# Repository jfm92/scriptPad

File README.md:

# scriptPad

The scriptPad project is a macroPad fully customizable with build in USB WebPage allowing to configure every aspect of the device without extra software or web page, everything you need in a single device.

## Work in progess

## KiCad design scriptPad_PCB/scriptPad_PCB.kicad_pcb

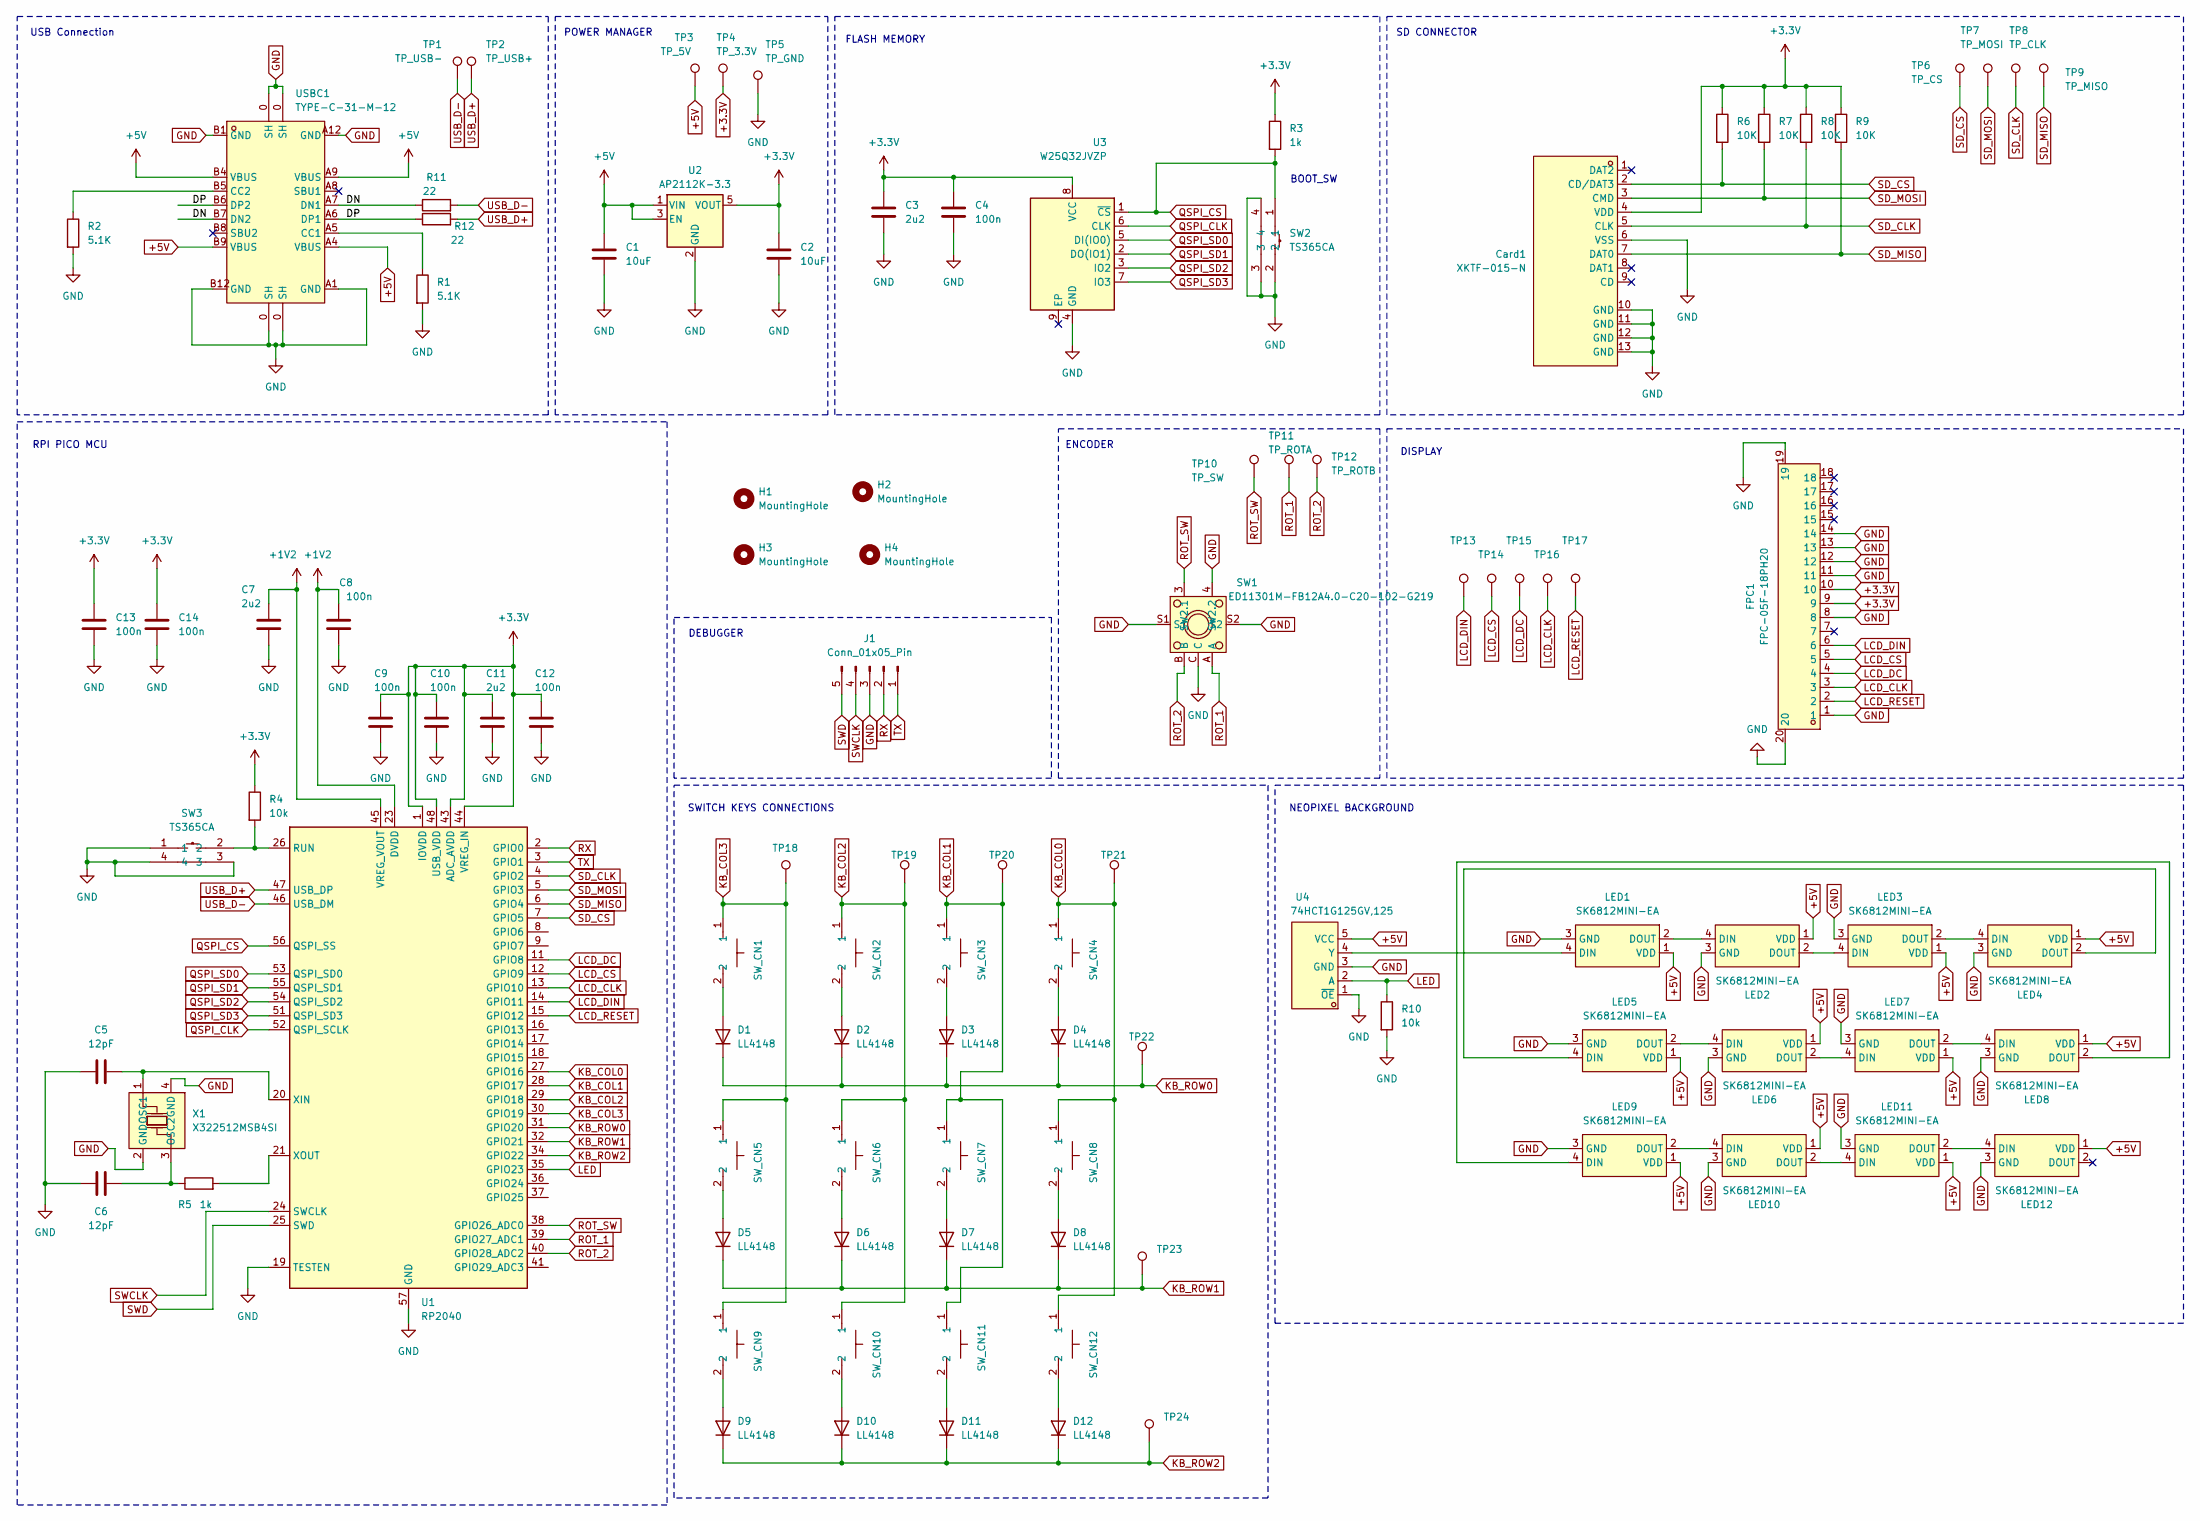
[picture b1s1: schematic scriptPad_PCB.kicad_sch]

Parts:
C1, C2: 10uF; C_0805_2012Metric; LCSC C17024
C3: 2u2; C_0805_2012Metric; LCSC C19110
C4: 100n; C_0603_1608Metric; LCSC C1591
C5, C6: 12pF; C_0603_1608Metric
C7, C11: 2u2; C_0805_2012Metric
C8, C9, C10, C12, C13, C14: 100n; C_0603_1608Metric
Card1: XKTF-015-N; TF-SMD_XKTF-015-N; LCSC Part C381082
D1: LL4148; D_MiniMELF; LCSC C2891733
D2, D3, D4, D5, D6, D7, D8, D9, D10, D11, D12: LL4148; D_MiniMELF
FPC1: FPC-05F-18PH20; FPC-SMD_18P-P0.50_FPC-05F-18PH20; LCSC Part C2856802
H1, H2, H3, H4: MountingHole; MountingHole_2.7mm_M2.5_Pad
J1: Conn_01x05_Pin; PinHeader_1x05_P1.27mm_Vertical
LED1, LED2, LED3, LED4, LED5, LED6, LED7, LED8, LED9, LED10, LED11, LED12: SK6812MINI-EA; LED-SMD_4P-L3.2-W2.8_SK6812MINI-EA; LCSC Part C5378731
R1, R2: 5.1K; R_0603_1608Metric; LCSC C156350
R3, R5: 1k; R_0805_2012Metric
R4, R10: 10k; R_0805_2012Metric
R6, R7, R8, R9: 10K; R_0805_2012Metric
R11, R12: 22; R_0603_1608Metric; LCSC C25295
SW1: ED11301M-FB12A4.0-C20-102-G219; SW-TH_CTR_ED11301M-FB12A4.0-C20-102-G219; LCSC Part C18213487
SW2, SW3: TS365CA; SW-SMD_TS365CA; LCSC Part C2681480
SW_CN1, SW_CN2, SW_CN3, SW_CN4, SW_CN5, SW_CN6, SW_CN7, SW_CN8, SW_CN9, SW_CN10, SW_CN11, SW_CN12: CPG151101S11-16; SMD_KEYBOARD-SW; LCSC Part C5156480
TP1: TP_USB-; TestPoint_Pad_D2.0mm
TP2: TP_USB+; TestPoint_Pad_D2.0mm
TP3: TP_5V; TestPoint_Pad_D2.0mm
TP4: TP_3.3V; TestPoint_Pad_D2.0mm
TP5: TP_GND; TestPoint_Pad_D2.0mm
TP6: TP_CS; TestPoint_Pad_D2.0mm
TP7: TP_MOSI; TestPoint_Pad_D2.0mm
TP8: TP_CLK; TestPoint_Pad_D2.0mm
TP9: TP_MISO; TestPoint_Pad_D2.0mm
TP10: TP_SW; TestPoint_Pad_D2.0mm
TP11: TP_ROTA; TestPoint_Pad_D2.0mm
TP12: TP_ROTB; TestPoint_Pad_D2.0mm
TP13, TP14, TP15, TP16, TP17, TP18, TP19, TP20, TP21, TP22, TP23, TP24: TestPoint; TestPoint_Pad_D2.0mm
U1: RP2040; QFN-56-1EP_7x7mm_P0.4mm_EP3.2x3.2mm
U2: AP2112K-3.3; SOT-23-5; LCSC C51118
U3: W25Q32JVZP; WSON-8-1EP_6x5mm_P1.27mm_EP3.4x4.3mm
U4: 74HCT1G125GV,125; SOT-753_L3.1-W1.7-P0.95-LS3.0-BL; LCSC Part C12502
USBC1: TYPE-C-31-M-12; USB-C_SMD-TYPE-C-31-M-12; LCSC Part C165948
X1: X322512MSB4SI; OSC-SMD_4P-L3.2-W2.5-BL; LCSC Part C9002

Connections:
+1V2: C7.1, C8.1, U1.23 (DVDD), U1.45 (VREG_VOUT), U1.50 (DVDD)
+3.3V: C2.1, C3.1, C4.1, C9.1, C10.1, C11.1, C12.1, C13.1, C14.1, Card1.4 (VDD), FPC1.9, FPC1.10, R3.1, R4.1, R6.1, R7.1, R8.1, R9.1, TP4.1, U1.1 (IOVDD), U1.10 (IOVDD), U1.22 (IOVDD), U1.33 (IOVDD), U1.42 (IOVDD), U1.43 (ADC_AVDD), U1.44 (VREG_IN), U1.48 (USB_VDD), U1.49 (IOVDD), U2.5 (VOUT), U3.8 (VCC)
+5V: C1.1, LED1.1 (VDD), LED2.1 (VDD), LED3.1 (VDD), LED4.1 (VDD), LED5.1 (VDD), LED6.1 (VDD), LED7.1 (VDD), LED8.1 (VDD), LED9.1 (VDD), LED10.1 (VDD), LED11.1 (VDD), LED12.1 (VDD), TP3.1, U2.1 (VIN), U2.3 (EN), U4.5 (VCC), USBC1.A4 (VBUS), USBC1.A9 (VBUS), USBC1.B4 (VBUS), USBC1.B9 (VBUS)
/DN: R11.1, USBC1.A7 (DN1), USBC1.B7 (DN2)
/DP: R12.1, USBC1.A6 (DP1), USBC1.B6 (DP2)
GND: C1.2, C2.2, C3.2, C4.2, C5.2, C6.2, C7.2, C8.2, C9.2, C10.2, C11.2, C12.2, C13.2, C14.2, Card1.6 (VSS), Card1.10 (GND), Card1.11 (GND), Card1.12 (GND), Card1.13 (GND), FPC1.1, FPC1.8, FPC1.11, FPC1.12, FPC1.13, FPC1.14, FPC1.19, FPC1.20, J1.3, LED1.3 (GND), LED2.3 (GND), LED3.3 (GND), LED4.3 (GND), LED5.3 (GND), LED6.3 (GND), LED7.3 (GND), LED8.3 (GND), LED9.3 (GND), LED10.3 (GND), LED11.3 (GND), LED12.3 (GND), R1.2, R2.2, R10.2, SW1.4 (SW2.2), SW1.C, SW1.S1, SW1.S2, SW2.2, SW2.3, SW2.4, SW3.1, SW3.3, SW3.4, TP5.1, U1.19 (TESTEN), U1.57 (GND), U2.2 (GND), U3.4 (GND), U4.1 (~OE), U4.3 (GND), USBC1.0 (SH), USBC1.A1 (GND), USBC1.A12 (GND), USBC1.B1 (GND), USBC1.B12 (GND), X1.2 (GND), X1.4 (GND)
KB_COL0: SW_CN4.1, SW_CN8.1, SW_CN12.1, TP21.1, U1.27 (GPIO16)
KB_COL1: SW_CN3.1, SW_CN7.1, SW_CN11.1, TP20.1, U1.28 (GPIO17)
KB_COL2: SW_CN2.1, SW_CN6.1, SW_CN10.1, TP19.1, U1.29 (GPIO18)
KB_COL3: SW_CN1.1, SW_CN5.1, SW_CN9.1, TP18.1, U1.30 (GPIO19)
KB_ROW0: D1.1 (K), D2.1 (K), D3.1 (K), D4.1 (K), TP22.1, U1.31 (GPIO20)
KB_ROW1: D5.1 (K), D6.1 (K), D7.1 (K), D8.1 (K), TP23.1, U1.32 (GPIO21)
KB_ROW2: D9.1 (K), D10.1 (K), D11.1 (K), D12.1 (K), TP24.1, U1.34 (GPIO22)
LCD_CLK: FPC1.3, TP16.1, U1.13 (GPIO10)
LCD_CS: FPC1.5, TP14.1, U1.12 (GPIO9)
LCD_DC: FPC1.4, TP15.1, U1.11 (GPIO8)
LCD_DIN: FPC1.6, TP13.1, U1.14 (GPIO11)
LCD_RESET: FPC1.2, TP17.1, U1.15 (GPIO12)
LED: R10.1, U1.35 (GPIO23), U4.2 (A)
unnamed: D1.2 (A), SW_CN1.2
unnamed: D2.2 (A), SW_CN2.2
unnamed: D3.2 (A), SW_CN3.2
unnamed: D4.2 (A), SW_CN4.2
unnamed: D5.2 (A), SW_CN5.2
unnamed: D6.2 (A), SW_CN6.2
unnamed: D7.2 (A), SW_CN7.2
unnamed: D8.2 (A), SW_CN8.2
unnamed: D9.2 (A), SW_CN9.2
unnamed: D10.2 (A), SW_CN10.2
unnamed: D11.2 (A), SW_CN11.2
unnamed: D12.2 (A), SW_CN12.2
unnamed: LED1.4 (DIN), U4.4 (Y)
unnamed: LED1.2 (DOUT), LED2.4 (DIN)
unnamed: LED2.2 (DOUT), LED3.4 (DIN)
unnamed: LED3.2 (DOUT), LED4.4 (DIN)
unnamed: LED4.2 (DOUT), LED5.4 (DIN)
unnamed: LED5.2 (DOUT), LED6.4 (DIN)
unnamed: LED6.2 (DOUT), LED7.4 (DIN)
unnamed: LED7.2 (DOUT), LED8.4 (DIN)
unnamed: LED8.2 (DOUT), LED9.4 (DIN)
unnamed: LED9.2 (DOUT), LED10.4 (DIN)
unnamed: LED10.2 (DOUT), LED11.4 (DIN)
unnamed: LED11.2 (DOUT), LED12.4 (DIN)
unnamed: R4.2, SW3.2, U1.26 (RUN)
unnamed: C5.1, U1.20 (XIN), X1.1 (OSC1)
unnamed: R5.2, U1.21 (XOUT)
unnamed: R1.1, USBC1.A5 (CC1)
unnamed: R2.1, USBC1.B5 (CC2)
unnamed: C6.1, R5.1, X1.3 (OSC2)
QSPI_CLK: U1.52 (QSPI_SCLK), U3.6 (CLK)
QSPI_CS: R3.2, SW2.1, U1.56 (QSPI_SS), U3.1 (~CS)
QSPI_SD0: U1.53 (QSPI_SD0), U3.5 (DI(IO0))
QSPI_SD1: U1.55 (QSPI_SD1), U3.2 (DO(IO1))
QSPI_SD2: U1.54 (QSPI_SD2), U3.3 (IO2)
QSPI_SD3: U1.51 (QSPI_SD3), U3.7 (IO3)
ROT_1: SW1.A, TP11.1, U1.39 (GPIO27_ADC1)
ROT_2: SW1.B, TP12.1, U1.40 (GPIO28_ADC2)
ROT_SW: SW1.3 (SW2.1), TP10.1, U1.38 (GPIO26_ADC0)
RX: J1.2, U1.2 (GPIO0)
SD_CLK: Card1.5 (CLK), R8.2, TP8.1, U1.4 (GPIO2)
SD_CS: Card1.2 (CD/DAT3), R6.2, TP6.1, U1.7 (GPIO5)
SD_MISO: Card1.7 (DAT0), R9.2, TP9.1, U1.6 (GPIO4)
SD_MOSI: Card1.3 (CMD), R7.2, TP7.1, U1.5 (GPIO3)
SWCLK: J1.4, U1.24 (SWCLK)
SWD: J1.5, U1.25 (SWD)
TX: J1.1, U1.3 (GPIO1)
USB_D+: R12.2, TP2.1, U1.47 (USB_DP)
USB_D-: R11.2, TP1.1, U1.46 (USB_DM)

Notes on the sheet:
DEBUGGER
NEOPIXEL BACKGROUND
DISPLAY
POWER MANAGER
SD CONNECTOR
SWITCH KEYS CONNECTIONS
BOOT_SW
ENCODER
RPI PICO MCU
USB Connection
FLASH MEMORY

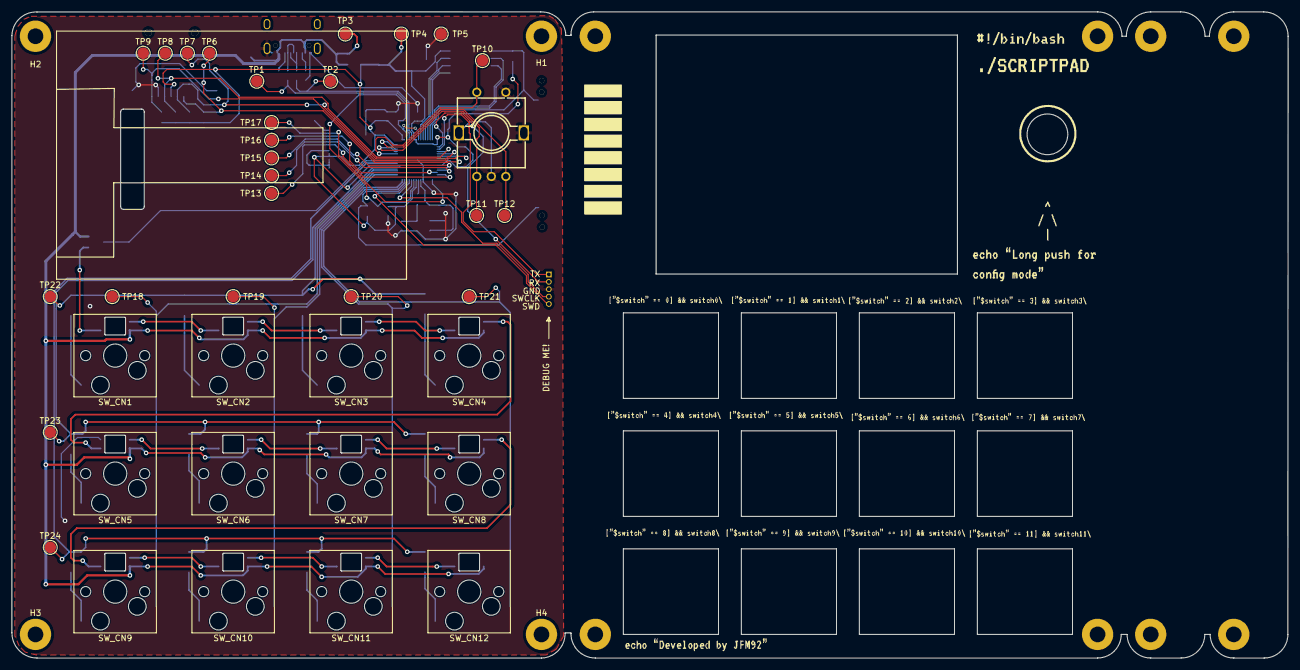
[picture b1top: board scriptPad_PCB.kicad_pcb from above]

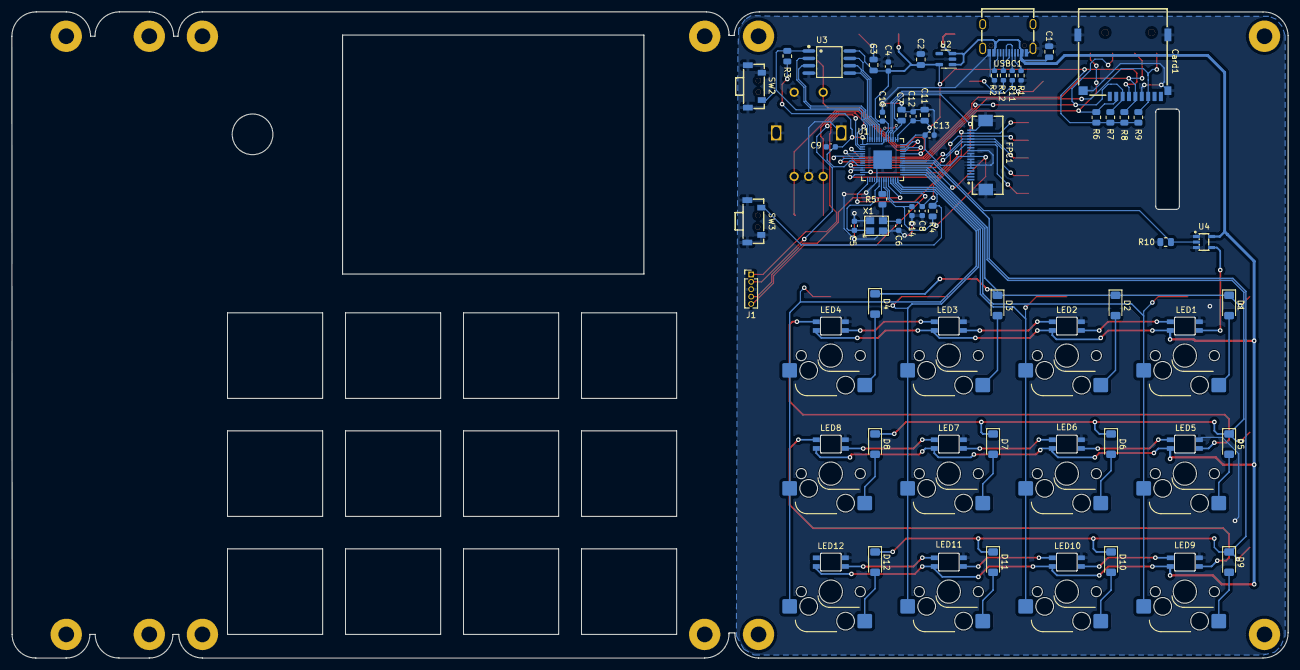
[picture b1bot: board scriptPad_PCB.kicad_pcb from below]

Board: 2 copper layers, 219.7 x 111.3 mm, 103 parts (61 on the bottom side), 68 nets.

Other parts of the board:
H4#2: MountingHole; MountingHole_2.7mm_M2.5_Pad

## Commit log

2023-10-10 Initial basic commit
2023-10-10 Adding initial github CI
2023-10-11 Adding FreeRTOS to the project
2023-10-12 Adding class to handle switch control/init
2023-10-16 Improving class encapsulation to avoid global variables ussage to interact between class and callbacks
2023-10-16 Initial implementation of HID management
2023-10-17 Implementing macros cache save and management
2023-10-17 Adding pico-filesystem library
2023-10-17 Updating pico-sdk route
2023-10-17 Changing FreeRTOS location to libraries folder
2023-10-17 Adding cJSON library to the project
2023-10-18 Adding class to manage internal flash files
2023-10-18 Temporary using of a local modify version
2023-10-18 Rework to use cJSON library to get switch configuration
2023-10-18 Comming back to previous pico-filesystem repo
2023-10-18 Deleting not necessary library and adding for have trace
2023-10-19 Adding to project required files to handle a USB Modem
2023-10-19 Basic implementation to transform the device into an USB Modem
2023-10-20 Adding singletone to fileManagement class
2023-10-20 Some little rework to delete non necessay friend functions and moving some variable initialization
2023-10-20 Adding tool to transform web project into .c and folder where to save web page files
2023-10-20 Making available external webPage ussage
2023-10-21 Basic implementation of ST7789V driver
2023-10-23 Moving display driver to GUI folder and adding function to draw incoming image matrix
2023-10-23 Adding LVGL library
2023-10-23 Some impovement on ST7789V class to allow extra configuration
2023-10-23 Moving LVGL submodule to libraries folder
2023-10-25 Rework to use a real switch matrix
2023-10-25 Adding launch profile to config gdb
2023-10-27 Adding a singletone to driver, to allow control from single instance
2023-10-27 Implementing a second message queue to send message to gui task
2023-10-27 New functionality to find and process files with previous configurations
2023-10-27 Adding new macro name field
2023-10-27 Changing LVGL config to allow groups control
2023-10-27 GUI management implementation
2023-11-01 Adding function to return macros names
2023-11-01 Fixing memory leak using CJSON lib
2023-11-01 Increasing freq, bufferlines and changing draw func
2023-11-01 Allowing to use two different USB descriptors
2023-11-01 First functional GUI menu
2023-11-02 Adding no-OS-FatFS-SD-SDIO-SPI-RPi-Pico library to manage SD card to save configs
2023-11-02 Removed pico-filesystem submodule
2023-11-02 General fixes due to it didn't like direct pointer
2023-11-04 Adding simple backlight WIP
2023-11-04 Ignoring specific vscode settings
2023-11-04 Adding first version of the main
2023-11-10 Adding initial version of the PCB
2023-11-13 Adding tinyUSB lib
2023-11-13 Modifications to allow use the newest and modded tinyUSB version
2023-11-16 Adding some initial frontend structure
2023-11-17 Adding dynamic profile and button matrix creation2
2023-11-23 Adding first functional version of modem frontEnd
2023-11-23 This should be autogenerated at compiling time, but for now...
2023-11-23 Creating new .json profile base on post response
2023-11-23 Script to regenerate frontend and build project at the same time
2023-11-24 Updating .json file model
2023-11-24 Adapting to handle new json content
2023-11-24 Some general improvements on JSON memory management
2023-11-24 Allowing to program sleep inside macros and fixing error which didn't allow to send duplicated characters
2023-11-24 Improving screen GUI
2023-11-25 Fixing partial screen update
2023-11-27 LVGL config optimization
2023-11-28 Implementing initial encoder management
2023-12-01 Adapting screen configuration for the final 2,4 model
2023-12-01 Fixing corrupted character when writes to SD
2023-12-29 Set right screen orientation
2023-12-29 Updating key codes and fix on IP address shown on config menu
2023-12-29 Setting GPIO config for the matrix on latest PCB model
2023-12-29 Updating neopixel number and disabling enconder by now
2023-12-29 Little modification on usb descriptors to easily identify on console
2023-12-29 Updating build project script
2023-12-29 Adding initial building instructions
2023-12-29 Updating PCB to new version
2024-01-08 Small update to show device
2024-01-13 Increasing CPU freq and disabling some animations to heavily increase performance
2024-01-16 Changing encoder pins from a generic list to ID - GPIO
2024-01-16 Fnctional implementation of rotatory encoder to set ID on each rotation and simple/long pulse implementation
2024-01-16 Making available the encoder on system initialization
2024-01-16 Modifiation to allow received json data bigger in chunks
2024-01-20 Adding funcitonality to get next/previous macro profile
